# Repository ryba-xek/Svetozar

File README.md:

# Svetozar: an open-source e-vehicles peripherals controller

View this project on [CADLAB.io](https://cadlab.io/project/1290).

_Current project status_: in active development. Some features work, some don't.

## In a nutshell:

This ~30$ device allows you to control headlights/turn signals/horn/fan/etc on a typical e-bike/e-scooter.

It consists of a [‘Blue pill’](https://wiki.stm32duino.com/index.php?title=Blue_Pill) board with STM32F103 microcontroller which is widely available
on eBay or [Aliexpress](https://www.aliexpress.com/af/STM32F103C8T6.html?site=glo&origin=n&spm=2114.search0604.0.0.7f4960689ztJHF&filterCat=400103%2C200215223%2C200084026&jump=afs&groupsort=1&SearchText=STM32F103C8T6&SortType=price_asc&initiative_id=SB_20181031001708)
and a custom board with high-voltage circuitry. (You can order this board at [jlcpcb.com](https://jlcpcb.com/) for around 11$/10 pcs delivered.)

An external 12V power source is required. The device is able to switch 6x 12V outputs plus 3x 12..100V outputs
(12..100V nets are optically isolated). One of the 12V outputs is intended to drive a high-current fan and generates a stabilized 0..12V current
for a smooth fan speed control. CAN bus is also supported, so you can write some code to interact with other CAN devices.
There are 11 inputs on the left side, most of them are digital and trigger when connected to ground. ABRK input is analog and accepts voltages up to 5V,
ATEMP input should be used with KTY84/130 temperature sensor (or NTC10k, but you'll have to change input resistors to match the sensor).

## Current functions:

- Stoplight has medium brightness when not triggered
- ABRK & DBRK trigger stoplight to full brightness with a starting blink
- LTURN, RTURN, WARN trigger (left/right/both) turn signals flash with ~1 Hz frequency
- LBEAM triggers LBEAM output
- HBEAM triggers both LBEAM & HBEAM outputs
- HORN triggers HORN output
- AUX triggers AUX output
- BLGHT triggers BLGHT output
- ATEMP can be programmed to smoothly control FAN output
- 12V net triggers current protection at ~25A peak, this disables all 12V outputs 
- BATT+ net triggers current protection at ~12A peak, this disables all 12..100V outputs

## Hardware requirements

* Blue pill board
* Main board with all the components soldered ([BOM](bom.pdf))
* ST-Link/V2 or V2-1 programmer (V1 is supported via native ST software under Windows)

## Firmware requirements

* [Arduino IDE](https://www.arduino.cc/en/Main/Software)
* Arduino SAM boards (Cortex-M3) support installed from Ardiuno IDE's boards manager
* [coddingtonbear's fork](https://github.com/coddingtonbear/Arduino_STM32) of Arduino STM32 ‘hardware’ files with hardware CAN support (`HardwareCAN` git branch)
* [STM32duino bootloader](https://github.com/rogerclarkmelbourne/STM32duino-bootloader/raw/master/binaries/generic_boot20_pc13.bin) for Blue pill boards
* Some STM32 [ST-Link/V2](https://github.com/pavelrevak/pystlink) or [USB-TTL](https://www.st.com/content/st_com/en/products/development-tools/software-development-tools/stm32-software-development-tools/stm32-programmers/flasher-stm32.html) flashing software

## Flashing a Blue Pill board with the bootloader

### Mac OS X
#### Requirements
##### Software
* python 3.x (brew install python)
* libusb (brew reinstall libusb)
* pyusb (pip3 install pyusb)
* [pystlink](https://github.com/pavelrevak/pystlink)

#### Process
1. Download [STM32duino bootloader](https://github.com/rogerclarkmelbourne/STM32duino-bootloader/raw/master/binaries/generic_boot20_pc13.bin)
2. Connect ST-Link programmer to the board
3. Flash it with
```shell
    pystlink --cpu STM32F103xB flash:erase:verify:generic_boot20_pc13.bin
```
4. Reset or re-connect the board

### Windows
#### To Do

#### Flashing via USB-TTL adapter under Windows
[Please read this russian article](https://habr.com/post/395577/)

## Installing Arduino with STM32duino support
[STM32duino installation instructions](https://github.com/rogerclarkmelbourne/Arduino_STM32/wiki/Installation)

### Mac OS X
1. Install Arduino
2. Install libusb (brew install libusb)
3. Launch Arduino IDE, go to Tools -> Board: ... -> Boards Manager and install the Arduino SAM boards (Cortex-M3) support.
4. Download [coddingtonbear's fork](https://github.com/coddingtonbear/Arduino_STM32) of Arduino STM32 ‘hardware’ files
with hardware CAN support, checkout `HardwareCAN` branch and move and rename it to ```~/Documents/Arduino/hardware/Arduino_STM32```.
5. In Arduino IDE select Tools -> Board: ... -> Generic STM32F103C series.
5. In Arduino IDE select Tools -> CPU speed(MHz): -> 48MHz.

## Credits
Blue pill board library is from [github/sagarHackeD](https://github.com/sagarHackeD/STM32Bluepill_eagle)
VOM1271T.lbr, MAX3051ESA.lbr & MC14504BDR2G.lbr are from [SnapEDA](https://www.snapeda.com/)

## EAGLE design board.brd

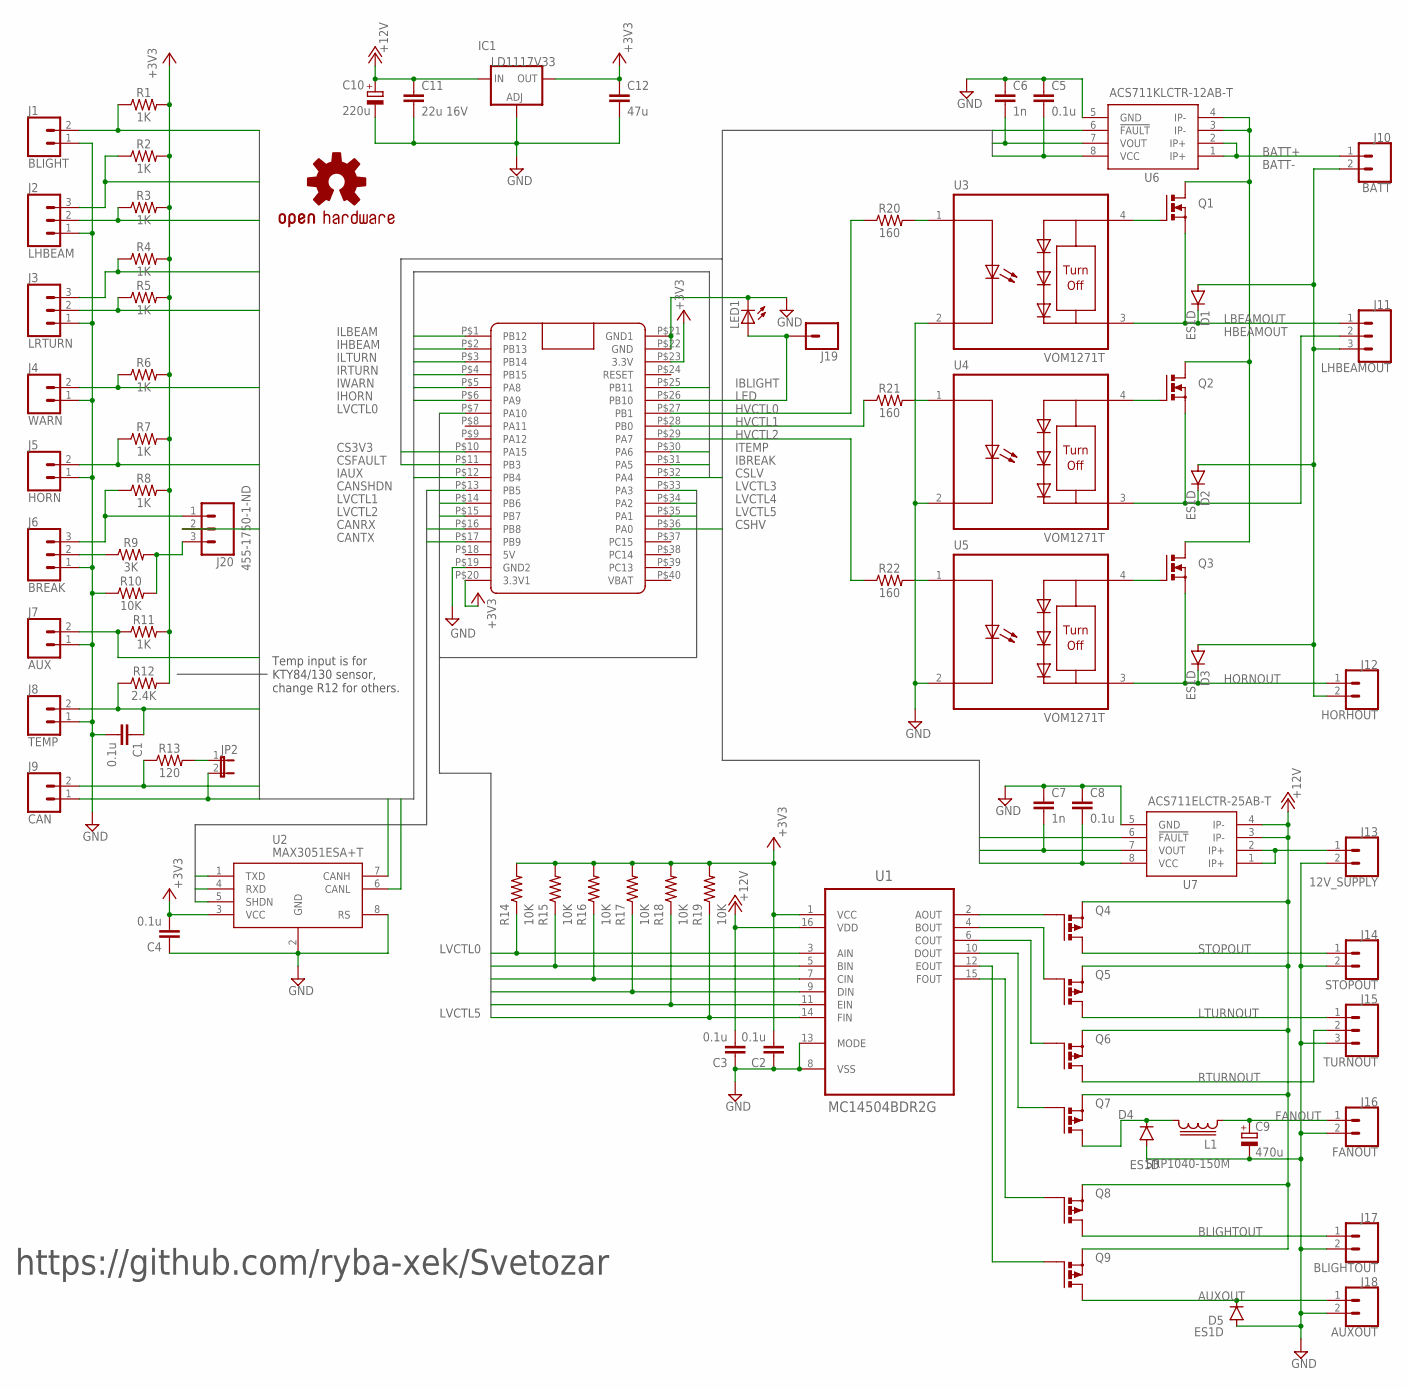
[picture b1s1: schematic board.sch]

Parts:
C1, C2, C4, C5, C8: 0.1u; C0805; MPN CC0805KRX7R9BB104
C3: 0.1u; C1206; MPN CC1206KRX7R8BB104
C6, C7: 1n; C0805; MPN CL21B102KBANNNC
C9: 470u; E3,5-8; MPN SK016M0470B3F-0811
C10: 220u; E2,5-6; MPN SK016M0220BZF-0611
C11: 22u 16V; C1206; MPN CL31A226KOHNNNE
C12: 47u; C1206; MPN CL31A476MQHNNNE
D1, D2, D3, D4, D5: ES1D; DO214AC; MPN ES1D
IC1: LD1117V33; DPACK; MPN NCP1117DT33G
J1: BLIGHT; SCREWTERMINAL-3.5MM-2; MPN DG350-3.5-02P-14-00AH
J2: LHBEAM; SCREWTERMINAL-3.5MM-3; MPN DG350-3.5-03P-14-00AH
J3: LRTURN; SCREWTERMINAL-3.5MM-3; MPN DG350-3.5-03P-14-00AH
J4: WARN; SCREWTERMINAL-3.5MM-2; MPN DG350-3.5-02P-14-00AH
J5: HORN; SCREWTERMINAL-3.5MM-2; MPN DG350-3.5-02P-14-00AH
J6: BREAK; SCREWTERMINAL-3.5MM-3; MPN DG350-3.5-03P-14-00AH
J7: AUX; SCREWTERMINAL-3.5MM-2; MPN DG350-3.5-02P-14-00AH
J8: TEMP; SCREWTERMINAL-3.5MM-2; MPN DG350-3.5-02P-14-00AH
J9: CAN; SCREWTERMINAL-3.5MM-2; MPN DG350-3.5-02P-14-00AH
J10: BATT; SCREWTERMINAL-3.5MM-2; MPN DG350-3.5-02P-14-00AH
J11: LHBEAMOUT; SCREWTERMINAL-3.5MM-3; MPN DG350-3.5-03P-14-00AH
J12: HORHOUT; SCREWTERMINAL-3.5MM-2; MPN DG350-3.5-02P-14-00AH
J13: 12V_SUPPLY; SCREWTERMINAL-3.5MM-2; MPN DG350-3.5-02P-14-00AH
J14: STOPOUT; SCREWTERMINAL-3.5MM-2; MPN DG350-3.5-02P-14-00AH
J15: TURNOUT; SCREWTERMINAL-3.5MM-3; MPN DG350-3.5-03P-14-00AH
J16: FANOUT; SCREWTERMINAL-3.5MM-2; MPN DG350-3.5-02P-14-00AH
J17: BLIGHTOUT; SCREWTERMINAL-3.5MM-2; MPN DG350-3.5-02P-14-00AH
J18: AUXOUT; SCREWTERMINAL-3.5MM-2; MPN DG350-3.5-02P-14-00AH
J19: CONN_01; 1X01; MPN PLS-1
J20: 455-1750-1-ND; 1X03; MPN PLS-3
JP2: JP1E; JP1; MPN PLS-2
L1: SRP1040-150M; SRP1040; MPN SRP1040-150M
LED1: LEDSML0805; SML0805; MPN KPT-2012ZGC
LOGO1: OSHW-LOGOL; OSHW-LOGO-L
Q1, Q2, Q3: PHP20NQ20T; TO220BV; MPN PHP20NQ20T.127
Q4, Q5, Q6, Q7, Q8, Q9: P-MOSFET-SO8; SO-08; MPN IRF7424TRPBF
R1, R2, R3, R4, R5, R6, R7, R8, R11: 1K; 0603; MPN RC0603JR-071KL
R9: 3K; 0603; MPN RC0603JR-073KL
R10, R14, R15, R16, R17, R18, R19: 10K; 0603; MPN RC0603JR-0710KL
R12: 2.4K; 0603; MPN RC0603FR-072K4L
R13: 120; 0603; MPN RC0603FR-07120RL
R20, R21, R22: 160; 0603; MPN RC0603FR-07160RL
U1: MC14504BDR2G; SOIC127P600X175-16N; MPN MC14504BDR2G
U2: MAX3051ESA+T; SO-08; MPN MAX3051ESA+T
U3, U4, U5: VOM1271T; SOIC254P695X242-4N; MPN VOM1271T
U6: ACS711KLCTR-12AB-T; SO08; MPN ACS711KLCTR-12AB-T
U7: ACS711ELCTR-25AB-T; SO08; MPN ACS711ELCTR-25AB-T
U$1: BLUE_PILL

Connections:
12V_IN: J13.1, U7.1 (IP+), U7.2 (IP+)
+3V3: C2.2, C4.2, C12.1, IC1.4 (OUT), R1.2, R2.2, R3.2, R4.2, R5.2, R6.2, R7.2, R8.2, R11.2, R12.2, R14.2, R15.2, R16.2, R17.2, R18.2, R19.2, U1.1 (VCC), U2.3 (VCC), U$1.P$20 (3.3V1), U$1.P$23 (3.3V)
+12V: C3.2, C10.+, C11.1, IC1.3 (IN), Q4.1 (S), Q4.2 (S), Q4.3 (S), Q5.1 (S), Q5.2 (S), Q5.3 (S), Q6.1 (S), Q6.2 (S), Q6.3 (S), Q7.1 (S), Q7.2 (S), Q7.3 (S), Q8.1 (S), Q8.2 (S), Q8.3 (S), Q9.1 (S), Q9.2 (S), Q9.3 (S), U1.16 (VDD), U7.3 (IP-), U7.4 (IP-)
AUXOUT: D5.C, J18.1, Q9.5 (D), Q9.6 (D), Q9.7 (D), Q9.8 (D)
BATT+: J10.1, U6.1 (IP+), U6.2 (IP+)
BATT-: D1.A, D2.A, D3.A, J10.2, J11.3, J12.2
BLIGHTOUT: J17.1, Q8.5 (D), Q8.6 (D), Q8.7 (D), Q8.8 (D)
CANH: J9.1, JP2.2, U2.7 (CANH)
CANL: J9.2, R13.1, U2.6 (CANL)
CANRX: U2.4 (RXD), U$1.P$16 (PB8)
CANSHDN: U2.5 (SHDN), U$1.P$13 (PB5)
CANTX: U2.1 (TXD), U$1.P$17 (PB9)
CS3V3: C5.2, C8.2, U6.8 (VCC), U7.8 (VCC), U$1.P$10 (PA15)
CSFAULT: U6.6 (!FAULT), U7.6 (!FAULT), U$1.P$11 (PB3)
CSHV: C6.2, U6.7 (VOUT), U$1.P$36 (PA0)
CSLV: C7.2, U7.7 (VOUT), U$1.P$32 (PA4)
FANOUT: C9.+, J16.1, L1.1
FANPWM: D4.C, L1.2, Q7.5 (D), Q7.6 (D), Q7.7 (D), Q7.8 (D)
GND: C1.2, C2.1, C3.1, C4.1, C5.1, C6.1, C7.1, C8.1, C9.-, C10.-, C11.2, C12.2, D4.A, D5.A, IC1.1 (ADJ), J1.1, J2.1, J3.1, J4.1, J5.1, J6.1, J7.1, J8.1, J13.2, J14.2, J15.3, J16.2, J17.2, J18.2, LED1.C, R10.1, U1.8 (VSS), U1.13 (MODE), U2.2 (GND), U2.8 (RS), U3.2 (C1), U4.2 (C1), U5.2 (C1), U6.5 (GND), U7.5 (GND), U$1.P$19 (GND2), U$1.P$21 (GND1), U$1.P$22 (GND)
HBEAMOUT: D2.C, J11.2, Q2.S, U4.3 (C2)
HORNOUT: D3.C, J12.1, Q3.S, U5.3 (C2)
HV: Q1.D, Q2.D, Q3.D, U6.3 (IP-), U6.4 (IP-)
HVCTL0: R20.1, U$1.P$27 (PB1)
HVCTL1: R21.1, U$1.P$28 (PB0)
HVCTL2: R22.1, U$1.P$29 (PA7)
IAUX: J7.2, R11.1, U$1.P$12 (PB4)
IBLIGHT: J1.2, R1.1, U$1.P$25 (PB11)
IBREAK: J20.2, U$1.P$31 (PA5)
IHBEAM: J2.2, R3.1, U$1.P$2 (PB13)
IHORN: J5.2, R7.1, U$1.P$6 (PA9)
ILBEAM: J2.3, R2.1, U$1.P$1 (PB12)
ILTURN: J3.3, R4.1, U$1.P$3 (PB14)
IRTURN: J3.2, R5.1, U$1.P$4 (PB15)
ITEMP: C1.1, J8.2, R12.1, U$1.P$30 (PA6)
IWARN: J4.2, R6.1, U$1.P$5 (PA8)
LBEAMOUT: D1.C, J11.1, Q1.S, U3.3 (C2)
LED: J19.1, LED1.A, U$1.P$26 (PB10)
LTURNOUT: J15.1, Q5.5 (D), Q5.6 (D), Q5.7 (D), Q5.8 (D)
LVCTL0: R14.1, U1.3 (AIN), U$1.P$7 (PA10)
LVCTL1: R15.1, U1.5 (BIN), U$1.P$14 (PB6)
LVCTL2: R16.1, U1.7 (CIN), U$1.P$15 (PB7)
LVCTL3: R17.1, U1.9 (DIN), U$1.P$33 (PA3)
LVCTL4: R18.1, U1.11 (EIN), U$1.P$34 (PA2)
LVCTL5: R19.1, U1.14 (FIN), U$1.P$35 (PA1)
LVG0: Q4.4 (G), U1.2 (AOUT)
LVG1: Q5.4 (G), U1.4 (BOUT)
LVG2: Q6.4 (G), U1.6 (COUT)
LVG3: Q7.4 (G), U1.10 (DOUT)
LVG4: Q8.4 (G), U1.15 (FOUT)
LVG5: Q9.4 (G), U1.12 (EOUT)
unnamed: J6.3, J20.1, R8.1
unnamed: JP2.1, R13.2
unnamed: J20.3, R9.2, R10.2
unnamed: J6.2, R9.1
unnamed: R20.2, U3.1 (A1)
unnamed: Q1.G, U3.4 (A2)
unnamed: R21.2, U4.1 (A1)
unnamed: Q2.G, U4.4 (A2)
unnamed: R22.2, U5.1 (A1)
unnamed: Q3.G, U5.4 (A2)
RTURNOUT: J15.2, Q6.5 (D), Q6.6 (D), Q6.7 (D), Q6.8 (D)
STOPOUT: J14.1, Q4.5 (D), Q4.6 (D), Q4.7 (D), Q4.8 (D)

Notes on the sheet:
https://github.com/ryba-xek/Svetozar
Temp input is for KTY84/130 sensor, change R12 for others.

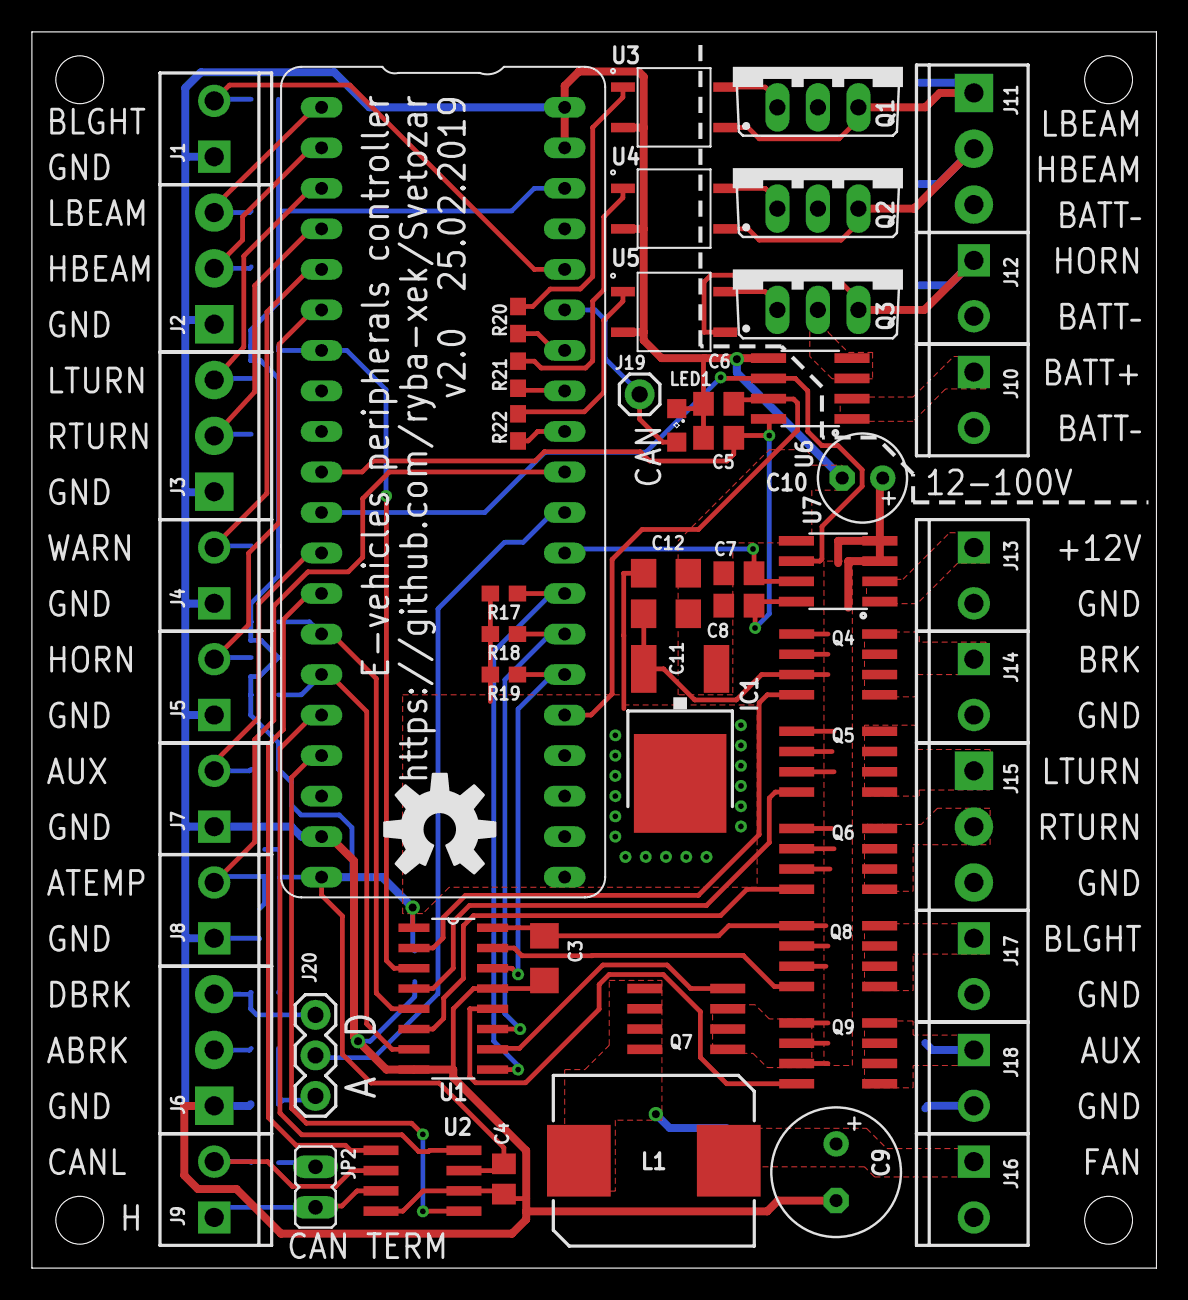
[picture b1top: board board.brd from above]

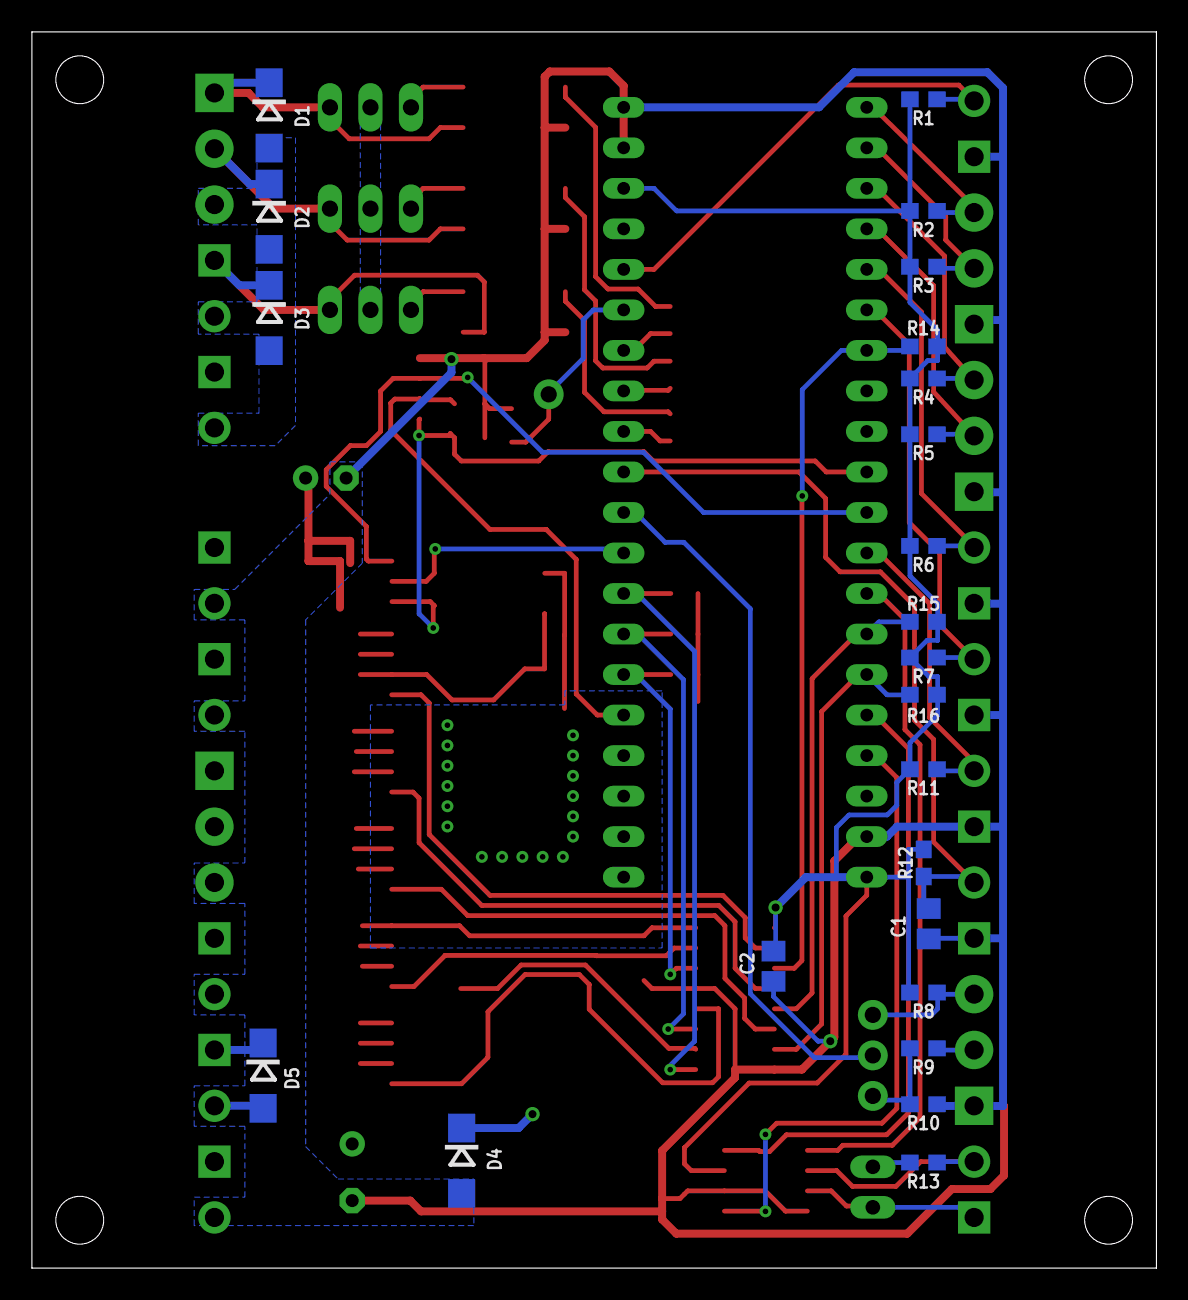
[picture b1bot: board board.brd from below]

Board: 2 copper layers, 70.5 x 77.5 mm, 81 parts (23 on the bottom side), 62 nets.

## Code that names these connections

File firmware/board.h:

/*
 * Svetozar: an open-source e-vehicles peripherals controller
 * Supported board version: v1.1
 *
 *
 * Pin assignments:
 *                               _________________
 *                              /       L__J      \
 *                Low beam in - | PB12        GND | -
 *               High beam in - | PB13        GND | -
 *               Left turn in - | PB14       3.3V | -
 *              Right turn in - | PB15      RESET | -
 *                 Warning in - | PA8        PB11 | - Backlight in
 *                    Horn in - | PA9        PB10 | - USART TX3 & LED
 * TIM1_CH3     Stoplight out - | PA10        PB1 | - Low beam out            TIM3_CH4
 *                       USB- - | PA11        PB0 | - High beam out           TIM3_CH3
 *                       USB+ - | PA12        PA7 | - Horn out                TIM3_CH2
 *                ACS711LC V+ - | PA15        PA6 | - Analog temp sensor in
 *             Overcurrent in - | PB3         PA5 | - A/D break in
 *                     Aux in - | PB4         PA4 | - LV current sense
 *            CAN IC shutdown - | PB5         PA3 | - Fan out                 TIM2_CH4
 * TIM4_CH1    Right turn out - | PB6         PA2 | - Backlight out           TIM2_CH3
 * TIM4_CH2     Left turn out - | PB7         PA1 | - Aux out                 TIM2_CH2
 *                     CAN Rx - | PB8         PA0 | - HV current sense
 *                     CAN Tx - | PB9        PC15 | - LSE oscillator in
 *                            - | 5V         PC14 | - LSE oscillator out
 *                            - | GND        PC13 | - Onboard LED out
 *                            - | 3.3V       VBAT |
 *                              \_________________/
 *
 * EXTi map:
 * EXTI0:
 * EXTI1:
 * EXTI2:
 * EXTI3: PB3 - Overcurrent in
 * EXTI4: PB4 - Aux in
 * EXTI5: PA5 - Break in
 * EXTI6:
 * EXTI7:
 * EXTI8: PA8 - Warning in
 * EXTI9: PA9 - Horn in
 * EXTI10:
 * EXTI11: PB11 - Backlight in
 * EXTI12: PB12 - Low beam in
 * EXTI13: PB13 - High beam in
 * EXTI14: PB14 - Left turn in
 * EXTI15: PB15 - Right turn in
 */


#ifndef BOARD_H
#define BOARD_H

#if F_CPU != 48000000UL
    #error "Please select Tools -> CPU Speed -> 48Mhz"
#endif


#define LBEAM_IN_PIN    PB12
#define HBEAM_IN_PIN    PB13
#define LTURN_IN_PIN    PB14
#define RTURN_IN_PIN    PB15
#define WARN_IN_PIN     PA8
#define HORN_IN_PIN     PA9
#define STOP_OUT_PIN    PA10
#define CSSUPPLY_PIN    PA15
#define CSFAULT_IN_PIN  PB3
#define AUX_IN_PIN      PB4
#define CAN_SHDN_PIN    PB5
#define RTURN_OUT_PIN   PB6
#define LTURN_OUT_PIN   PB7
#define CAN_RX_PIN      PB8
#define CAN_TX_PIN      PB9

#define BLIGHT_IN_PIN   PB11
#define LED2_OUT_PIN    PB10
#define LBEAM_OUT_PIN   PB1
#define HBEAM_OUT_PIN   PB0
#define HORN_OUT_PIN    PA7
#define ATEMP_IN_PIN    PA6
#define BREAK_IN_PIN    PA5
#define LVCS_IN_PIN     PA4
#define FAN_OUT_PIN     PA3
#define BLIGHT_OUT_PIN  PA2
#define AUX_OUT_PIN     PA1
#define HVCS_IN_PIN     PA0
#define LED_OUT_PIN     PC13

void BoardSetup(void (*callback)(void), void (*csFaultCallback)(void));

#endif //BOARD_H

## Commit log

2018-09-10 initial import
2018-09-10 Backlink to CADLAB.io has been added.
2018-10-06 Schematics v1
2018-10-06 PCB v.1
2018-10-06 Board & schematics v 1.1. Minor improvements
2018-10-06 Added export & design settings
2018-10-15 Added BOM
2018-10-31 first firmware version
2019-03-10 Board v2, firmware is still WIP
2019-03-10 BOM for v2
2019-03-10 minor v2 fixes
2019-07-25 Updated v2 code, added 3d print models

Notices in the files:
parts and their libraries:
SparkFun-Connectors: Licensing: Creative Commons ShareAlike 4.0 International - https://creativecommons.org/licenses/by-sa/4.0
inductor-bourns: Copyright (C) 2008, Bob Starr
